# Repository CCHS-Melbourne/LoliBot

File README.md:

# LoliBot - The ESP32 Based Soccer bot.

Quick links ...

  * [Hardware assembly](http://www.openhardwareconf.org/wiki/LoliBot-Assembly)
  * [Software installation and usage](software)

Welcome to the 2018 linux.conf.au Open Hardware Project.  You can see information about this and other MiniConfs at <http://www.openhardwareconf.org/wiki/Main_Page>.

If you're attending the assembly workshop at Linux.conf.au 2018, the place to start is <http://www.openhardwareconf.org/wiki/LoliBot>

This year's project is called the Lolibot, and is a simple robot is designed to chase and kick a Ping Pong ball around.

It features a Lolin32-lite ESP32 based chip as it's primary microprocessor and includes a MPU6050 6 axis accelerometer.

In order to reduce complexity and to be a bit more flexible with our design this years project is a platform with discrete components.
Those of you who are looking forward to the smell of melting solder won't be disappointed though, there are many headers, LEDS and switches to keep you busy.

## Hardware

### Screen Shots

### Assembly

Assembly instructions for the kit are at <http://www.openhardwareconf.org/wiki/LoliBot-Assembly>

### Hardware Links

* [WEMOS LOLIN32](https://wiki.wemos.cc/products:lolin32:lolin32)
* [mpu-6050](https://www.invensense.com/products/motion-tracking/6-axis/mpu-6050/) TBD lots of options
* [Wheels](https://www.aliexpress.com/item/TT-Motor-130motor-with-the-wheel-Smart-Car-Robot-Gear-Motor-for-Arduino-DC3V-6V-DC/32829319427.html) one of many like this..

### datasheets

* [L9110 Motor control driver chip](datasheets/datasheet-l9110.pdf)

## Software

All the usual ESP32 development options apply to the LoliBot ...

 * [microPython scripts](software)
 * Arduino IDE sketches
 * Native ESP-IDF FreeRTOS firmware

We've chosen to focus on using microPython to provide a simple, yet
capable entry point for newcomers to robotics and embedded computers.

The [software sub-directory has instructions](software)
 on installing and developing software for the LoliBot.

## LICENSE

Licensed under the TAPR Open Hardware License (<http://www.tapr.org/OHL>). The "license" sub-folder also contains a copy of this license in plain text format.

Copyright John Spencer, Angus Gratton, Andy Gelme, Jon Oxer, Mark Wolfe 2017

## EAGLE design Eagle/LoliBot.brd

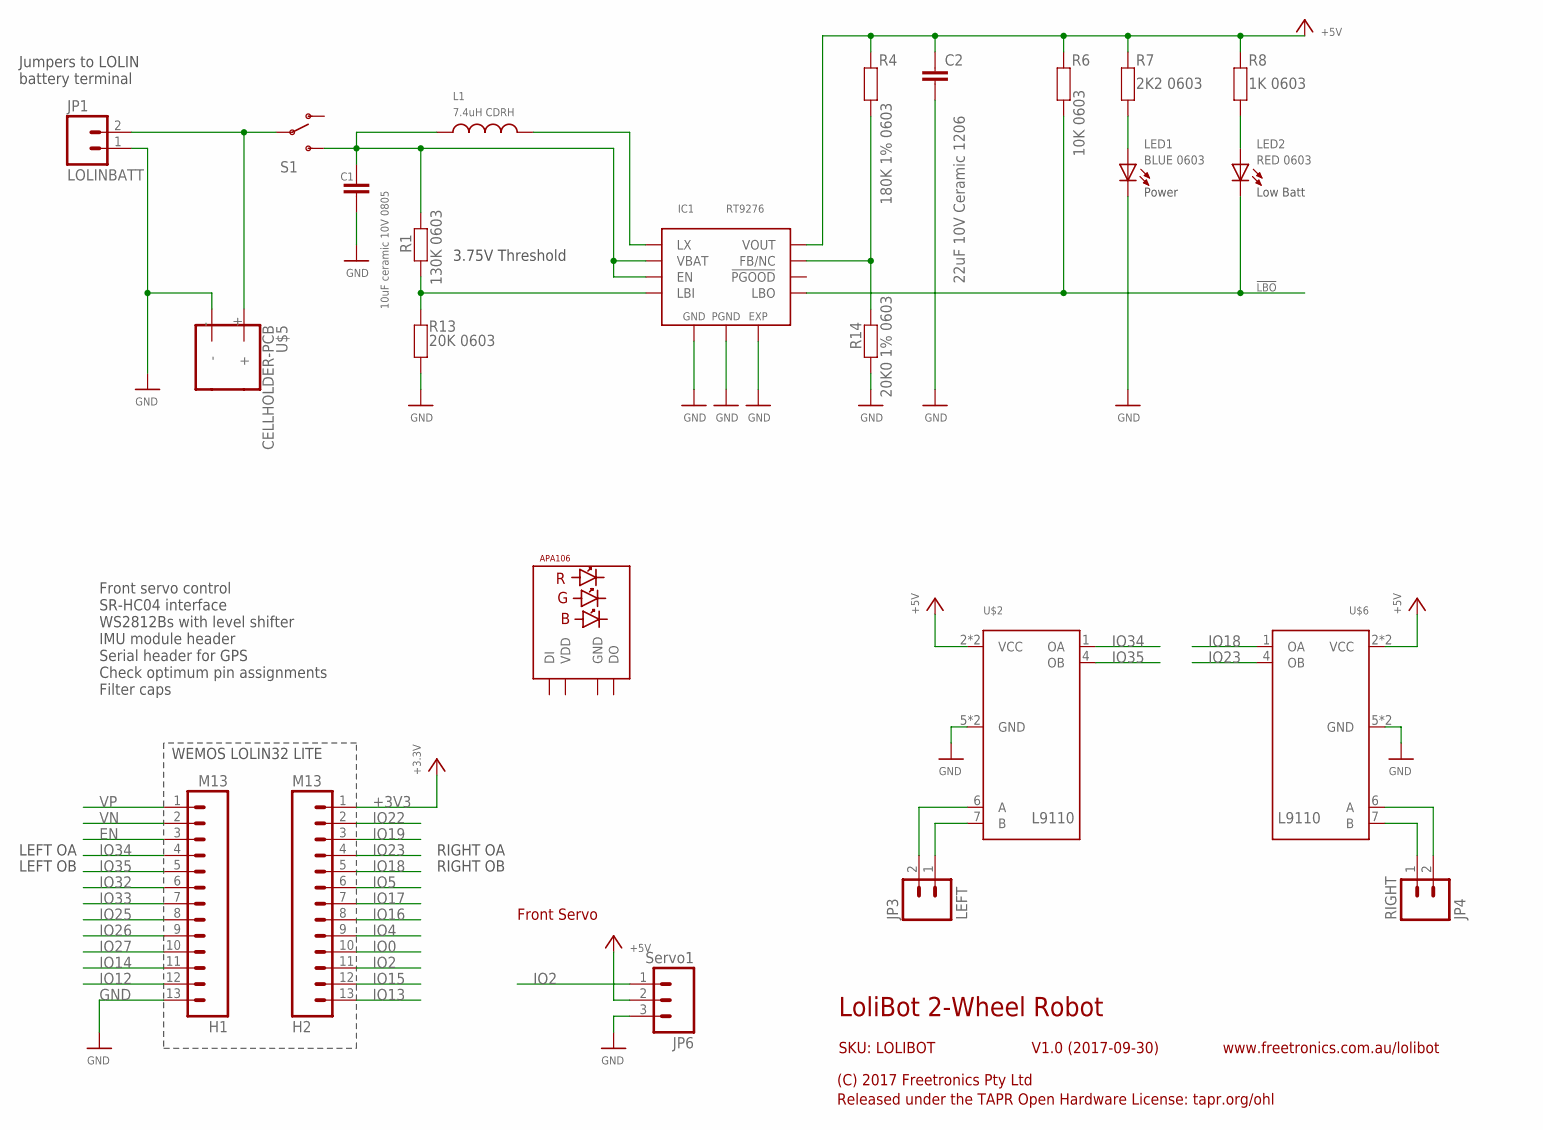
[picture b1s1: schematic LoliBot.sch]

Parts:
C1: 10uF ceramic 10V 0805; C0805
C2: 22uF 10V Ceramic 1206; C1206K
H1, H2: M13; 1X13
IC1: RT9276; WDFN-10L-3X3
JP1: LOLINBATT; SCREWTERMINAL-3.5MM-2
JP3: LEFT; SCREWTERMINAL-3.5MM-2
JP4: RIGHT; SCREWTERMINAL-3.5MM-2
JP6: Servo1; 1X03
L1: 7.4uH CDRH; CDRH
LED1: BLUE 0603; LED-0603
LED2: RED 0603; LED-0603
R1: 130K 0603; 0603
R4: 180K 1% 0603; 0603
R6: 10K 0603; 0603
R7: 2K2 0603; 0603
R8: 1K 0603; 0603
R13: 20K 0603; 0603
R14: 20K0 1% 0603; 0603
S1: SWITCH-SPSTPTH; SWITCH-SPDT
U$1: APA106F8; LED8MMRGB
U$2, U$6: L9110SO8; SO08
U$5: CELLHOLDER-PCB; BH-18650-PC

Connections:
!LBO: IC1.4 (LBO), LED2.C, R6.2
+3V3: H2.1
+5V: C2.1, IC1.2 (VOUT), JP6.2, R4.1, R6.1, R7.1, R8.1, U$2.2 (VCC), U$2.3 (VCC), U$6.2 (VCC), U$6.3 (VCC)
EN: H1.3
FB: IC1.3 (FB/NC), R4.2, R14.2
GND: C1.2, C2.2, H1.13, IC1.5 (GND), IC1.10 (PGND), IC1.EXP, JP1.1, JP6.3, LED1.C, R13.1, R14.1, U$1.2 (GND), U$2.5 (GND), U$2.8 (GND), U$5.-, U$6.5 (GND), U$6.8 (GND)
IO0: H2.10
IO2: H2.11, JP6.1
IO4: H2.9
IO5: H2.6
IO12: H1.12
IO13: H2.13
IO14: H1.11
IO15: H2.12
IO16: H2.8
IO17: H2.7
IO18: H2.5, U$6.1 (OA)
IO19: H2.3
IO22: H2.2
IO23: H2.4, U$6.4 (OB)
IO25: H1.8
IO26: H1.9
IO27: H1.10
IO32: H1.6
IO33: H1.7
IO34: H1.4, U$2.1 (OA)
IO35: H1.5, U$2.4 (OB)
LBI: IC1.7 (LBI), R1.1, R13.2
LX: IC1.9 (LX), L1.2
unnamed: JP3.1, U$2.7 (B)
unnamed: JP3.2, U$2.6 (A)
unnamed: JP4.1, U$6.7 (B)
unnamed: JP4.2, U$6.6 (A)
unnamed: JP1.2, S1.2, U$5.+
unnamed: LED1.A, R7.2
unnamed: LED2.A, R8.2
VBAT: C1.1, IC1.1 (EN), IC1.6 (VBAT), L1.1, R1.2, S1.3 (S)
VDD: U$1.3 (VDD)
VN: H1.2
VP: H1.1

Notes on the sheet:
LoliBot 2-Wheel Robot
V1.0 (2017-09-30)
(C) 2017 Freetronics Pty Ltd
Released under the TAPR Open Hardware License: tapr.org/ohl
www.freetronics.com.au/lolibot
SKU: LOLIBOT
Front Servo
Front servo control SR-HC04 interface WS2812Bs with level shifter IMU module header Serial header for GPS Check optimum pin assignments Filter caps
WEMOS LOLIN32 LITE
LEFT OA
LEFT OB
RIGHT OB
RIGHT OA
Low Batt
Power
3.75V Threshold
Jumpers to LOLIN battery terminal

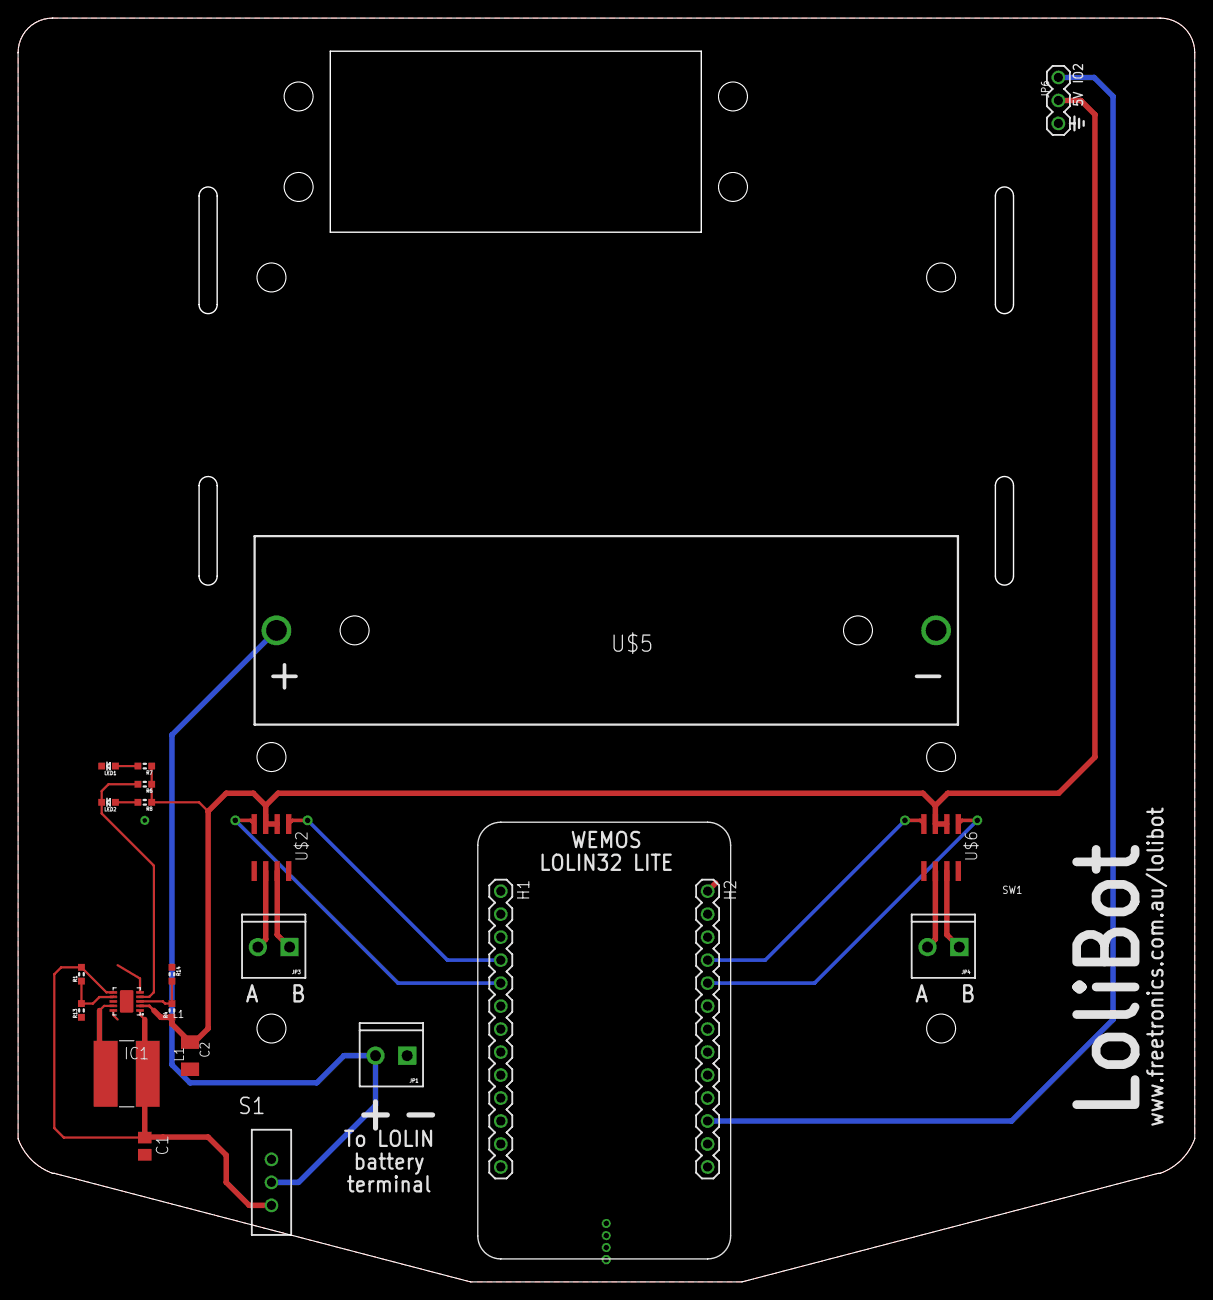
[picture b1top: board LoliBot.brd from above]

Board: 2 copper layers, 130.0 x 139.7 mm, 24 parts (1 on the bottom side), 19 nets.

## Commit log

2017-10-05 Initial starting point.
2017-10-09 Added rough concept in Eagle format
2017-10-09 Added PCB preview in PDF
2017-10-09 Created KiCAD Schematic
2017-10-10 feat(Layout) Added slots and drill holes based on the existing DXF
2017-10-11 Added 3d model of mock up.
2017-10-12 Added Battery Footprint
2017-10-13 Added footprint for lolibot-lite
2017-10-15 Added mpu-9250 module header and updated power pins.
    * Fixes to the l9110 library for power input
    * Fixes to the lolin32-lite library for power output
2017-10-15 Assigned some footprints and built out apa106 chain for underlights.
2017-10-15 Added datasheets and started assigning footprints.
2017-10-25 Added footprints
2017-10-25 Added Board for JS Version
2017-10-26 Updated lolin32-lite footprint
2017-11-01 Added Mounting brackets and IR sensor
2017-11-12 Updated footprint
    Improved motor driver positions.
    Rotated acel to match x/y directions
2017-11-16 Whoops, those L9110 Pins don't go there.
2017-11-17 Pin reassignment.
2017-11-20 Added expansion ports
2017-11-20 Moved Servo position
    to remove interference with expansion ports.
2017-11-20 Added Schematic PDF
2017-11-22 battery symbols reversed.
2017-11-26 Removed voltage boost.
2017-11-26 Updated renders
2017-11-30 wrong image. every damn time.
2017-12-07 Added Fuse. Updated pcb
2017-12-07 Added Through holes for cable ties
2017-12-10 Started silkscreen
2017-12-11 Added logos and text
    And vias.
2017-12-11 Added more text
2017-12-12 i2c pullup resistors
2017-12-13 Eagle files and datasheet removed
    To maintain consistency. The Eagle version is now out of date.
2017-12-13 Updated render link
2017-12-15 Final update for version 1.2
2017-12-19 Moved circuit locations
2017-12-19 Added LoliWrapper
2017-12-19 updated silkscreen
2017-12-20 fixed overhanging through holes.
    Board production house didn't like vias that get cut in half
2018-01-14 Initial LoliBot microPython software check-in.
2018-01-15 Temporarily hide "script/flash_lolibot.sh" failure to remove "boot.py".
2018-01-15 Correctly calculate 2D to 1D coordinates based on X-axis size.
2018-01-16 Move "configuration/wifi.py" to "configuration/wifi.py.template" and added ".gitignore" file.
2018-01-20 README.md: Update with some links to the OHMC2018 wiki
2018-01-20 Updated "flash_lolibot.sh" to use latest firmware.
2018-01-20 Initial documentation outline.
2018-01-20 Minor improvements to the main page link to the software instructions.
2018-01-20 Some quick links to useful information.
2018-01-20 Added instructions for Python and PIP installation.
2018-01-21 Added instructions for USB serial driver installation.
2018-01-21 Minor "software/ReadMe.md" improvements.
2018-01-21 Highlighting !
2018-01-21 Fix broken integer to string cast got motor frequency MQTT command.
2018-01-21 Completed development (host) computer software installation.
2018-01-21 Completed Wi-Fi configuration documentation.
2018-01-21 Completed MQTT configuration documentation.
2018-01-21 Some minor ReadMe.md improvements.
2018-01-22 Place a note against temporarily dead links.
2018-01-22 explain how to install and use pip3 on debian
2018-01-22 silly little interactive controller
2018-01-22 software/scripts: Split firmware flash and micropython update
    Add a 2nd script to update the micropython code separately from
    reflashing the firmware image
2018-01-22 mqtt: Catch exceptions in message handlers
    If a message handler throws an except because of some
    malformed input, catch it rather than letting it kill
    the main loop and dropping to a REPL.
2018-01-22 mqtt: Publish to the 'state' topic when booted
    Announce our existence to the world, making it easier
    to see which bots are alive
2018-01-22 Create I2C bus in the lolibot module
2018-01-22 mpu9250: Convert line endings to unix
2018-01-22 mpu9250: Basic accelerometer support
    Initialise the accelerometer, and once per second
    output the maximum / minimum reading. Needs hooking
    up to MQTT and other stuff
2018-01-22 mpu9250: Handle module not being installed gracefully
    Don't complain or print empty output if the accelerometer
    module is not installed
2018-01-22 Lolibot: Add 'servo' and 'motors' commands
    Support directly settings motor PWM controls
    motors (1023 0 1023 0) to go forward
    Support servo command 'servo [-100..100] for -100
    (backward spin) to 100 (forward spin) and 0 for stop
2018-01-22 Add link to OHMC LoliBot Software Presentation.
2018-01-22 MQTT via WebSocket example controller
2018-01-22 lolibot: Check the motors command comes with 4 args
2018-01-22 udp_control: Add a listener on port 4900 for control
    Receive commands with the same format as the MQTT
    endpoint directly on port 4900.
    Periodically sends a broadcast presence announcement
    to the network on that port too
2018-01-22 windows flash_lolibot script
2018-01-22 examples/controller.sh: default to stop
    Make any input that is not registered default to stop.
2018-01-22 examples/controller.sh: make sure we stop when exiting
    Add an exit trap so regardless of how the script is terminated
    the LoliBot will stop.
2018-01-22 examples/controller.sh: lookup the MQTT host from the configuration
    Saves having to update the MQTT host in multiple places.
2018-01-22 Removed dead links.

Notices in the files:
parts and their libraries:
freetronics-original: Licensing: CC v3.0 Share-Alike You are welcome to use this library for commercial purposes.
